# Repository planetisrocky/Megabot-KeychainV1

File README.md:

# Megabot Keychain

A Big Hero 6 inspired figure with a round display for a face. It shows emotions, the time, weather, and more, and you switch modes with buttons. Built for Hack Club's **Half Life** program.

## Planned Features

- 1.28" round display (GC9A01, 240x240) as the face
- Emotions switched with one of 3 buttons
- Time calibrated over WiFi (NTP)
- Weather and more modes to come
- I2S header for a MAX98357A amp and speaker (voice lines and UI sounds)
- Rechargeable single-cell LiPo, charged over USB-C through the XIAO

## Controls

| Button | What it does |
|---|---|
| BTN1 | Cycles through the emotions |
| BTN2 | Switches between face and time |
| BTN3 | Unused for now (reserved) |

## Hardware

| Part | Notes |
|---|---|
| Seeed XIAO ESP32-C3 | Brain, WiFi, LiPo charger |
| 1.28" GC9A01 round display | SPI, wired to J2 |
| 3x 6 mm tactile switches | Wired to J3 |
| Custom 2-layer round PCB | Files in this repo |
| 10k resistor (R1) | [what it does] |
| LiPo battery (planned) | Soldered to the XIAO's BAT+/BAT- pads |
| MAX98357A amp + speaker (planned) | Spare audio header J1 |

Prices and funding: see [BOM.md](BOM.md).

## Pin Map

| Signal | XIAO pin |
|---|---|
| DC / RST / CS | D1 / D2 / D3 |
| SCK / MOSI | D8 / D10 |
| BTN1 / BTN2 / BTN3 | D4 / D5 / D6 |
| Audio: LRC / BCLK / DIN | D0 / D9 / D7 |

## Simulation

Try the firmware in your browser: [Wokwi link](https://wokwi.com/projects/477629702640173057)

Wokwi has no round display, so a rectangular ILI9341 stands in for it. Colors stand in for the faces, and the clock is a fake one that starts at 12:00.

## Files

- `MegabotPCB.kicad_pro`, `.kicad_sch`, `.kicad_pcb`: KiCad 7 project
- `MegabotPCB-Gerbers.zip`: PCB fabrication files
- `firmware/`: Wokwi simulation code
- `BOM.md`: bill of materials
- `images/`: screenshots

## Opening the KiCad Project

The XIAO symbol and footprint come from Seeed's OPL_Kicad_Library on GitHub. Download it and add it in KiCad's library manager so the project opens without missing parts.

## Notes

Firmware started from an AI-generated sketch, then simplified and modified by me.

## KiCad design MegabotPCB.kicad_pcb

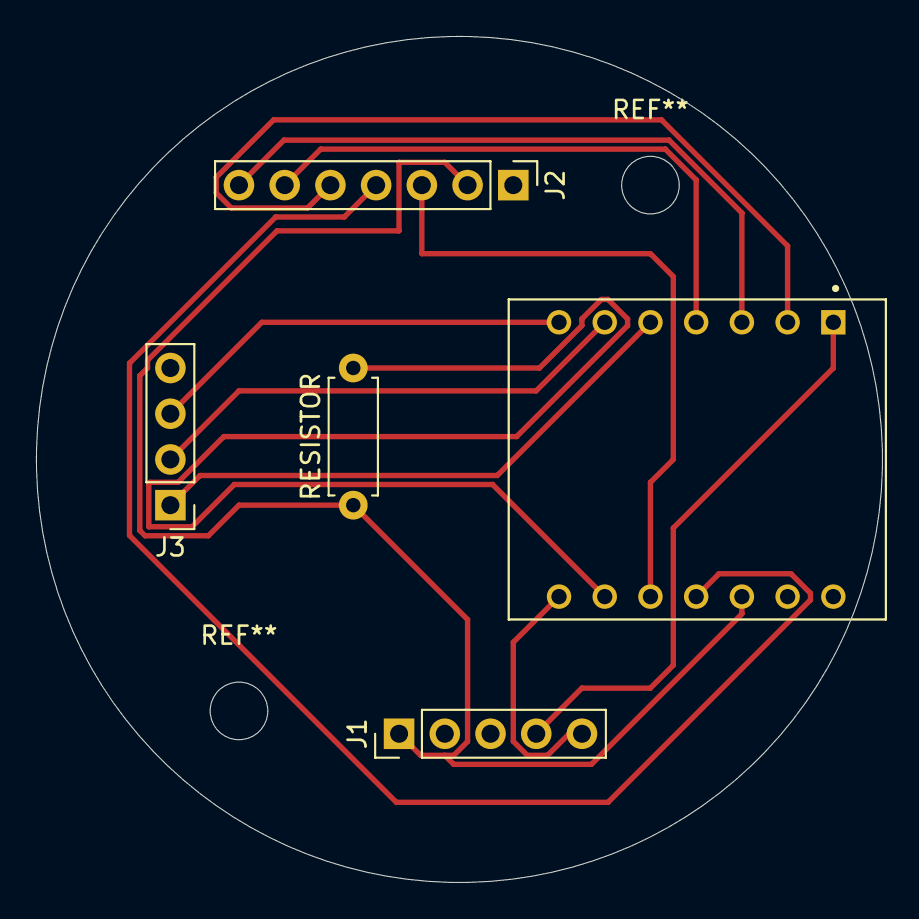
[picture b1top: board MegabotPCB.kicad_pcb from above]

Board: 2 copper layers, 47.0 x 47.0 mm, 5 parts (0 on the bottom side), 13 nets.

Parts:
J1: AUDIO; PinHeader_1x05_P2.54mm_Vertical
J2: SCREEN; PinHeader_1x07_P2.54mm_Vertical
J3: BUTTONS; PinHeader_1x04_P2.54mm_Vertical
RESISTOR: 10k; R_Axial_DIN0207_L6.3mm_D2.5mm_P7.62mm_Horizontal
U1: ESP32C3; MODULE_XIAO_ESP32C3

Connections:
+3V3: J1.1, J2.2, RESISTOR.1, U1.12 (VCC_3V3)
/BLCK: RESISTOR.2, U1.9 (D8)
/BTN1: J3.1, U1.5 (D4)
/BTN2: J3.2, U1.6 (D5)
/BTN3: J3.3, U1.7 (TX_D6)
/CS: J2.6, U1.4 (D3)
/DC: J2.5, U1.2 (D1)
/DIN: J1.5, U1.8 (RX_D7)
/LRC: J1.4, U1.1 (D0)
/MOSI: J2.4, U1.11 (D10)
/RST: J2.7, U1.3 (D2)
/SCK: J2.3, U1.10 (D9)
GND: J1.2, J2.1, J3.4, U1.13 (GND)
